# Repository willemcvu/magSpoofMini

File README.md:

# magSpoofMini
My (miniature) version of Samy Kamkar's magspoof project, which allows you to spoof credit and other magnetic cards.

These will be available on Tindie shortly (fully assembled).

# KiCad 3D board render

# Key features diagram

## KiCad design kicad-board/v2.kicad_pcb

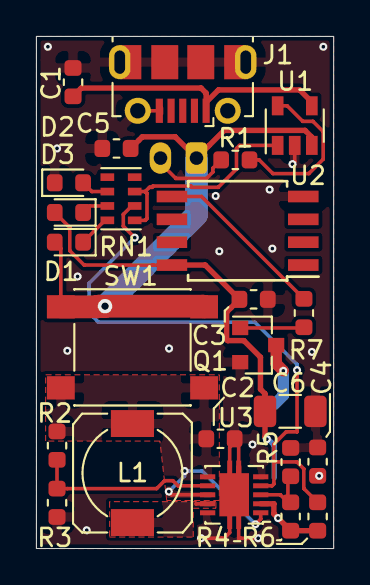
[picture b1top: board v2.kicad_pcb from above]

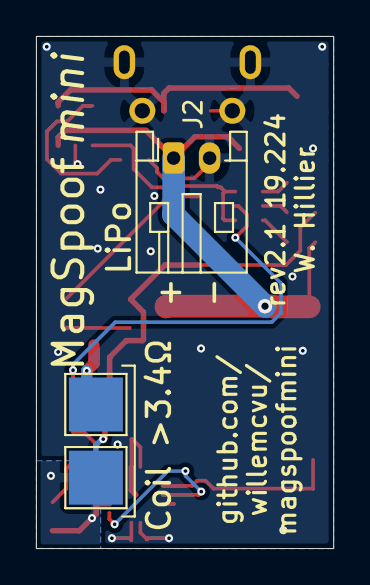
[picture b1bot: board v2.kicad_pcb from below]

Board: 2 copper layers, 16.5 x 28.4 mm, 27 parts (3 on the bottom side), 17 nets.

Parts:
C1, C3: 0.1u; C_0603_1608Metric
C2: 10u; C_0603_1608Metric
C4, C5: 4.7u; C_0603_1608Metric
C6: 100u; C_1206_3216Metric
D1: BLUE_LED; LED_0603_1608Metric
D2: GREEN_LED; LED_0603_1608Metric
D3: RED_LED; LED_0603_1608Metric
J1: USB_B_Micro; USB_Micro-B_Molex-105017-0001
J2: LiPO; JST_PH_S2B-PH-K_1x02_P2.00mm_Horizontal
L1: 6.8uH; L_B82462G4_6.3mmx3mm
Q1: Q_NMOS_GDS; SOT-23
R1: 47k; R_0603_1608Metric
R2: 1M; R_0603_1608Metric
R3, R5: 180k; R_0603_1608Metric
R4: 1.6M; R_0603_1608Metric
R6: R5; R_0603_1608Metric
R7: 1k; R_0603_1608Metric
RN1: 1k; R_Cat16-4
SW1: SW_Push; SW_SPST_PTS645
TP3: COIL1; TestPoint_Pad_3.0x3.0mm
TP4: COIL2; TestPoint_Pad_3.0x3.0mm
U1: MCP73831-2-OT; SOT-23-5
U2: ATtiny85-20SU; SOIJ-8_5.3x5.3mm_P1.27mm
U3: TPS6102x; VSON-10-1EP_3x3mm_P0.5mm_EP1.65x2.4mm

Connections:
+5V: C3.1, C4.1, C6.1, D3.2, R4.1, R6.1, TP3.1, U2.8, U3.2
+BATT: C5.1, D1.2, J2.1, SW1.1, U1.3
+VSW: C2.1, L1.1, R2.1, SW1.2, U3.1, U3.6, U3.8
/BATT_LOW_LED: R6.2, RN1.2, U3.4
/CHG_LED: RN1.1, RN1.3, U1.1
/COIL2: Q1.3, TP4.1
/COIL_CTRL: R7.2, U2.5
GND: C1.2, C2.2, C3.2, C4.2, C5.2, C6.2, D2.1, J1.5, J1.6, J2.2, Q1.2, R1.2, R3.2, R5.2, U1.2, U2.4, U3.5, U3.10, U3.11
unnamed: D1.1, RN1.8
unnamed: D2.2, RN1.6
unnamed: D3.1, RN1.7
unnamed: L1.2, U3.9
unnamed: Q1.1, R7.1
unnamed: R1.1, U1.5
unnamed: R2.2, R3.1, U3.7
unnamed: R4.2, R5.1, U3.3
VBUS: C1.1, J1.1, U1.4

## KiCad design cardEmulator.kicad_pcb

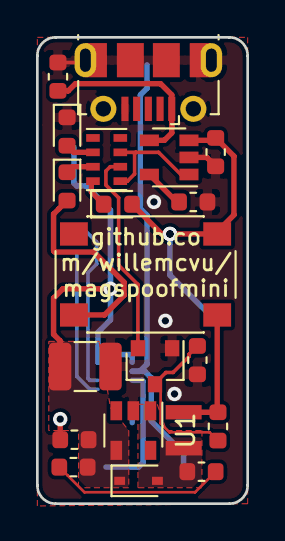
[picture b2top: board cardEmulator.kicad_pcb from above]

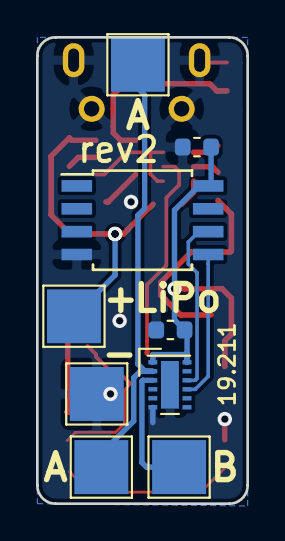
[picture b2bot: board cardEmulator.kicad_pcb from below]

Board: 2 copper layers, 11.7 x 25.9 mm, 29 parts (9 on the bottom side), 18 nets.

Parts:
C1, C4, C5: 10uF; C_0603_1608Metric
C2: 120pF; C_0603_1608Metric
C3, C6: 0.1uF; C_0603_1608Metric
C7: 100uF; C_1210_3225Metric
D1: BLUE_LED; LED_0603_1608Metric
D2: GREEN_LED; LED_0603_1608Metric
D3: RED_LED; LED_0603_1608Metric
D4: SMD22WS-TP; D_SOD-323
J1: USB_B_Micro; USB_Micro-B_Molex-105017-0001
L1: L; Inductor_1008_Metric2520
R1: 47k; R_0603_1608Metric
R2: 5.1; R_0603_1608Metric
R4: 39k; R_0603_1608Metric
R7: 10k; R_0603_1608Metric
RN1: 1k; R_Cat16-4
SW1: SW_Push; SW_SPST_PTS645-custom-silkscreen
TP1, TP1#2: COIL1; TestPoint_Pad_3.0x3.0mm
TP2: COIL2; TestPoint_Pad_3.0x3.0mm
TP3: +BATT; TestPoint_Pad_3.0x3.0mm
TP4: -BATT; TestPoint_Pad_3.0x3.0mm
U1: TPS613222A; SOT-23-5
U2: MCP73831-2-OT; SOT-23-5
U3: ATtiny85-20SU; SOIJ-8_5.3x5.3mm_P1.27mm
U4: TPS3839DBZ; SOT-23
U5: DRV8835; WSON-12-1EP_3x2mm_P0.5mm_EP1x2.65

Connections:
+5V: C2.1, C3.1, C4.1, C6.1, C7.1, D4.1, U1.4, U3.8, U5.1, U5.12
+BATT: C5.1, D1.2, SW1.1, TP3.1, U2.3
+VSW: D3.2, L1.1, R7.1, SW1.2
/BATT_LOW_LED: RN1.2, U4.2
/BR1: U3.5, U5.9
/BR2: U3.6, U5.10
/CHG_LED: RN1.1, RN1.3, U2.1
/COIL1: TP1.1, TP1#2.1, U5.2
/COIL2: TP2.1, U5.3
GND: C1.2, C3.2, C4.2, C5.2, C6.2, C7.2, D2.1, J1.5, J1.6, R1.2, R4.2, TP4.1, U1.2, U2.2, U3.4, U4.1, U5.6, U5.13
unnamed: C2.2, R2.1
unnamed: D1.1, RN1.8
unnamed: D2.2, RN1.6
unnamed: D3.1, RN1.7
unnamed: D4.2, L1.2, R2.2, U1.1
unnamed: R1.1, U2.5
unnamed: R4.1, R7.2, U4.3
VBUS: C1.1, J1.1, U2.4

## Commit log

2019-02-12 Publishing PCB.
2019-07-31 rev2 released
    - Fixed 5V boost converter footprint (U1, TPS5613222A) to be DBZ version, which is SOT23-5
    - Added better silkscreen documentation
2019-07-31 made rev2 gerbers
2019-07-31 v2 done
2019-07-31 new diagram + cleaned up directory
2019-07-31 New better readme
2019-08-13 Made new board
2019-08-13 Updated silkscreen, shipped board
2019-08-14 Updated resistor values
